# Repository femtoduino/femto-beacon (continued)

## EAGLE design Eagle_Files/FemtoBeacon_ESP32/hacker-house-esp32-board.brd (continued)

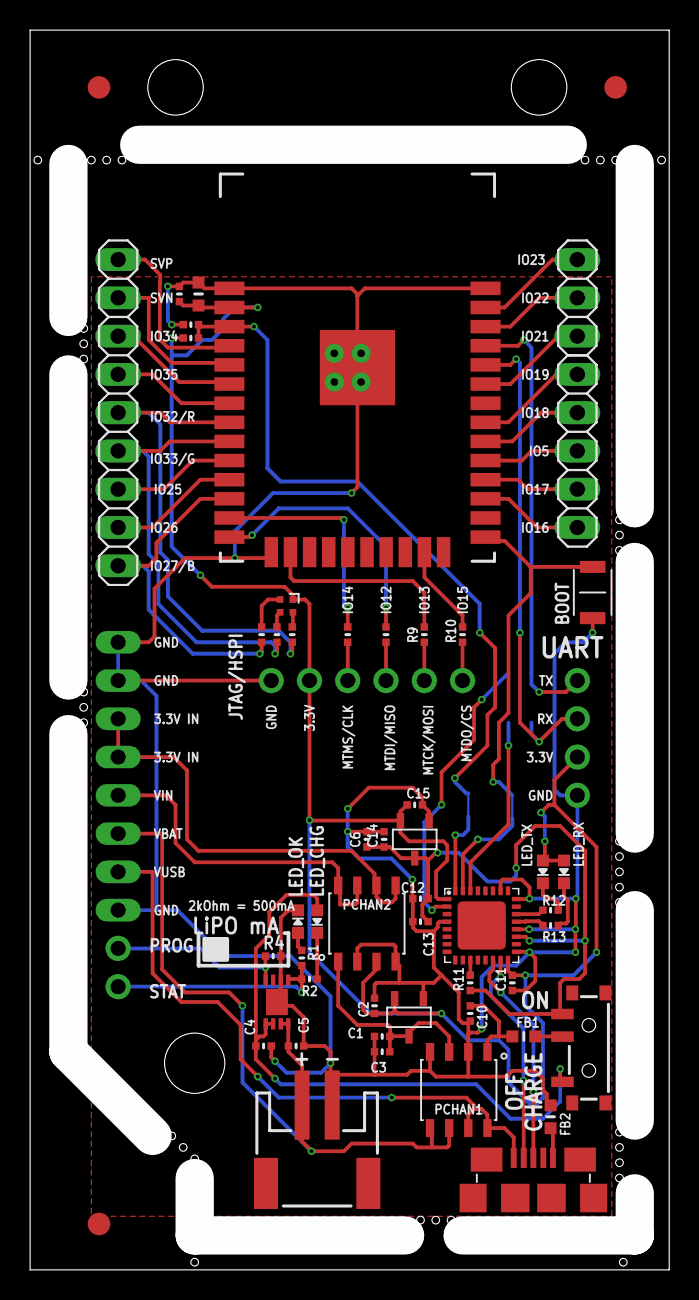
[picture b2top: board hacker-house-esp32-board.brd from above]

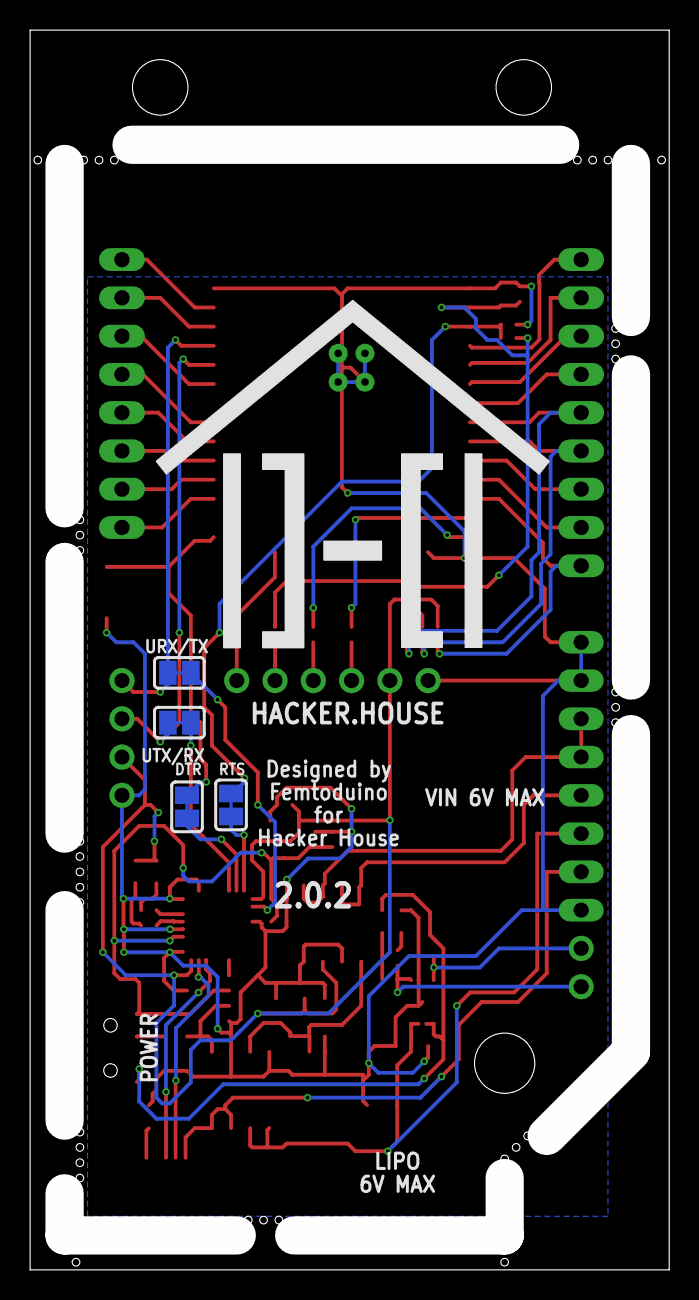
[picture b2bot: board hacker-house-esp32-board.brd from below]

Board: 2 copper layers, 42.4 x 82.3 mm, 62 parts (4 on the bottom side), 57 nets.

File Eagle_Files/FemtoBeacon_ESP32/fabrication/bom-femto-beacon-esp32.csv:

"Qty";"Value";"Device";"Package";"Parts";"Description";"MF";"MPN";"OC_FARNELL";"OC_NEWARK";
"2";"";"FERRITE_0603MP";"_0603MP";"FB1, FB2";"Ferrite Bead";"";"";"";"";
"2";"";"HEADER-1X1ROUND";"1X01_ROUND";"PROG, STAT";"PIN HEADER";"";"";"";"";
"1";"";"HEADER-1X4ROUND";"1X04_ROUND";"UART";"PIN HEADER";"";"";"";"";
"1";"";"HEADER-1X6SMT";"1X06_SMT";"JTAG";"PIN HEADER";"";"";"";"";
"1";"";"HEADER-1X7ROUND";"1X07_ROUND";"SPI";"PIN HEADER";"";"";"";"";
"1";"";"HEADER-1X8";"1X08_OVAL";"POWER";"PIN HEADER";"";"";"";"";
"1";"";"JST_2PIN";"JSTPH2";"CN_BATT_CHARGE";"JST 2-Pin Right-Angle Connector";"";"S2B-PH-SM4-TB(LF)(SN)";"";"";
"1";"";"PINHD-1X3";"1X03";"JP4";"PIN HEADER";"";"";"";"";
"1";"";"PINHD-1X6";"1X06";"JP3";"PIN HEADER";"";"";"";"";
"1";"";"PINHD-1X9";"1X09";"JP1";"PIN HEADER";"";"";"";"";
"3";"";"RESISTOR_0402MP";"_0402MP";"R14, R15, R16";"Resistors";"";"";"";"";
"3";"";"SOLDERJUMPERCLOSED";"SOLDERJUMPER_CLOSEDWIRE";"SJ1, SJ2, SJ3";"SMD Solder JUMPER";"";"";"";"";
"3";"";"SWITCH_SPDT";"SPDT_SMT_SSSS811101";"SWCHARGE, SWPOWER, SW_BATTMODE";"Switch - SPDT";"";"SSSS811101";"";"";
"6";"";"TESTPOINTROUND0.5MM";"TESTPOINT_ROUND_0.5MM";"TP1, TP2, TP3, TP4, TP5, TP6";"Test Point";"";"";"";"";
"1";"";"USB_TYPEA";"USB_A-SMT";"CN1";"USB - Type A Connectors";"";"36-931-ND";"";"";
"5";"0.1uF";"CAP_CERAMIC_0402MP";"_0402MP";"C6, C8, C9, C11, C13";"Ceramic Capacitors";"";"";"";"";
"1";"0.47uF";"CAP_CERAMIC_0402MP";"_0402MP";"C3";"Ceramic Capacitors";"";"";"";"";
"4";"100";"RESISTOR_0402MP";"_0402MP";"R7, R8, R9, R10";"Resistors";"";"";"";"";
"1";"100k";"RESISTOR_0402MP";"_0402MP";"R5";"Resistors";"";"";"";"";
"3";"10K";"RESISTOR_0402MP";"_0402MP";"R4, R6, R11";"Resistors";"";"";"";"";
"1";"10nF";"CAP_CERAMIC_0402MP";"_0402MP";"C10";"Ceramic Capacitors";"";"";"";"";
"1";"10uF";"CAP_CERAMIC_0603MP";"_0603MP";"C7";"Ceramic Capacitors";"";"";"";"";
"2";"2.2uF";"CAP_CERAMIC_0402MP";"_0402MP";"C1, C2";"Ceramic Capacitors";"";"";"";"";
"1";"2.5k";"RESISTOR_0402MP";"_0402MP";"R3";"Resistors";"";"";"";"";
"2";"221";"RESISTOR_0402MP";"_0402MP";"R1, R2";"Resistors";"";"";"";"";
"2";"270";"RESISTOR_0402MP";"_0402MP";"R12, R13";"Resistors";"";"";"";"";
"1";"3.3V";"MCP1700T-3302E/TT";"MCP1700T-3302E/TT";"LDO1";"Microchip LDO "MCP1700" in a 3-Pin SOT-23 package.";"";"MCP1700T-3302E/TT";"";"";
"3";"4.7uF";"CAP_CERAMIC_0402MP";"_0402MP";"C4, C5, C12";"Ceramic Capacitors";"";"";"";"";
"1";"ESP32-WROOM-32";"ESP32-WROOM-32";"ESP32-WROOM-32-MODULE";"MOD1";"ESP32 WiFi/Bluetooth module";"";"ESP32-WROOM-32";"";"";
"3";"FIDUCIAL";"FIDUCIAL";"FIDUCIAL_1MM";"FID1, FID2, FID3";"For use by pick and place machines to calibrate the vision/machine, 1mm";"";"";"";"";
"1";"FT232RQ";"FT232RQ";"QFN32";"IC1";"Source: http://www.ftdichip.com/Documents/DataSheets/DS_FT232R_v104.pdf";"";"FT232RQ";"1146033";"91K9919";
"3";"GREEN";"LED0603_NOOUTLINE";"CHIPLED_0603_NOOUTLINE";"LED_OK, LED_RX, LED_TX";"LED";"";"";"";"";
"1";"LRTB_R48G";"LRTB_R48G";"LRTB_R48G";"RGB1";"OSRAM RGB LED";"";"LRTB R48G";"";"";
"1";"MCP73831-2ACI/MC";"MCP73831-2ACI/MC";"2X3_DFN";"LIPO1";"";"";"MCP73831-2ACI/MC";"";"";
"1";"RED";"LED0603_NOOUTLINE";"CHIPLED_0603_NOOUTLINE";"LED_CHG";"LED";"";"";"";"";
"2";"SI4948BEY-T1-E3";"SI4948BEY-T1-E3";"SO-8";"PCHAN1, PCHAN2";"Vishay dual P-Channel Mosfet SI4948BEY-T1-E3";"";"SI4948BEY-T1-E3";"";"";
"1";"TACTILE_SWITCH_NO_GND_NO_BOSS";"TACTILE_SWITCH_NO_GND_NO_BOSS";"SIDE_ACT_NO_GND_NO_BOSS";"BOOT";"Omron tactile switch";"";"B3U-3000P";"";"";

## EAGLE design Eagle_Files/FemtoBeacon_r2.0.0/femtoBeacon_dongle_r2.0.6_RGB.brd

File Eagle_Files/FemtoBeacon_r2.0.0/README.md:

eagle-pcb-helpers
=================

A collection of JS utilities to help with Eagle PCB grunt work.

## Panelizer helper
A utility to help you panelize stuff outside the board size limits.

### Requires

 - Node http-server `npm install -g http-server`

### Usage
Use a terminal, navigate to this folder, and run `http-server ./`, then open up [https://localhost:8080/panelizer_helper.html](https://localhost:8080/panelizer_helper.html) in your favorite browser.

### About
Due to the artificially (and arbitrarily) imposed board size limitations of EAGLE PCB licensing, it becomes impossible to panelize large amounts of small boards.
This tool allows one to copy a column of board outlines, components, and text, and create the corresponding XML with updated part names (such as "IC1...IC5" to "IC6...IC10", etc), while applying a shift value to the X coordinates.

You still need to manually open the .brd file, and locate the last column of `<element>` nodes, but you can simply copy and paste that XML into this helper, set an X offset value, and process the text to generate the next column.

EAGLE PCB doesn't have any problem copying vias and traces outside the artificial boundry limits, so you really only need this tool for dimensions and components.

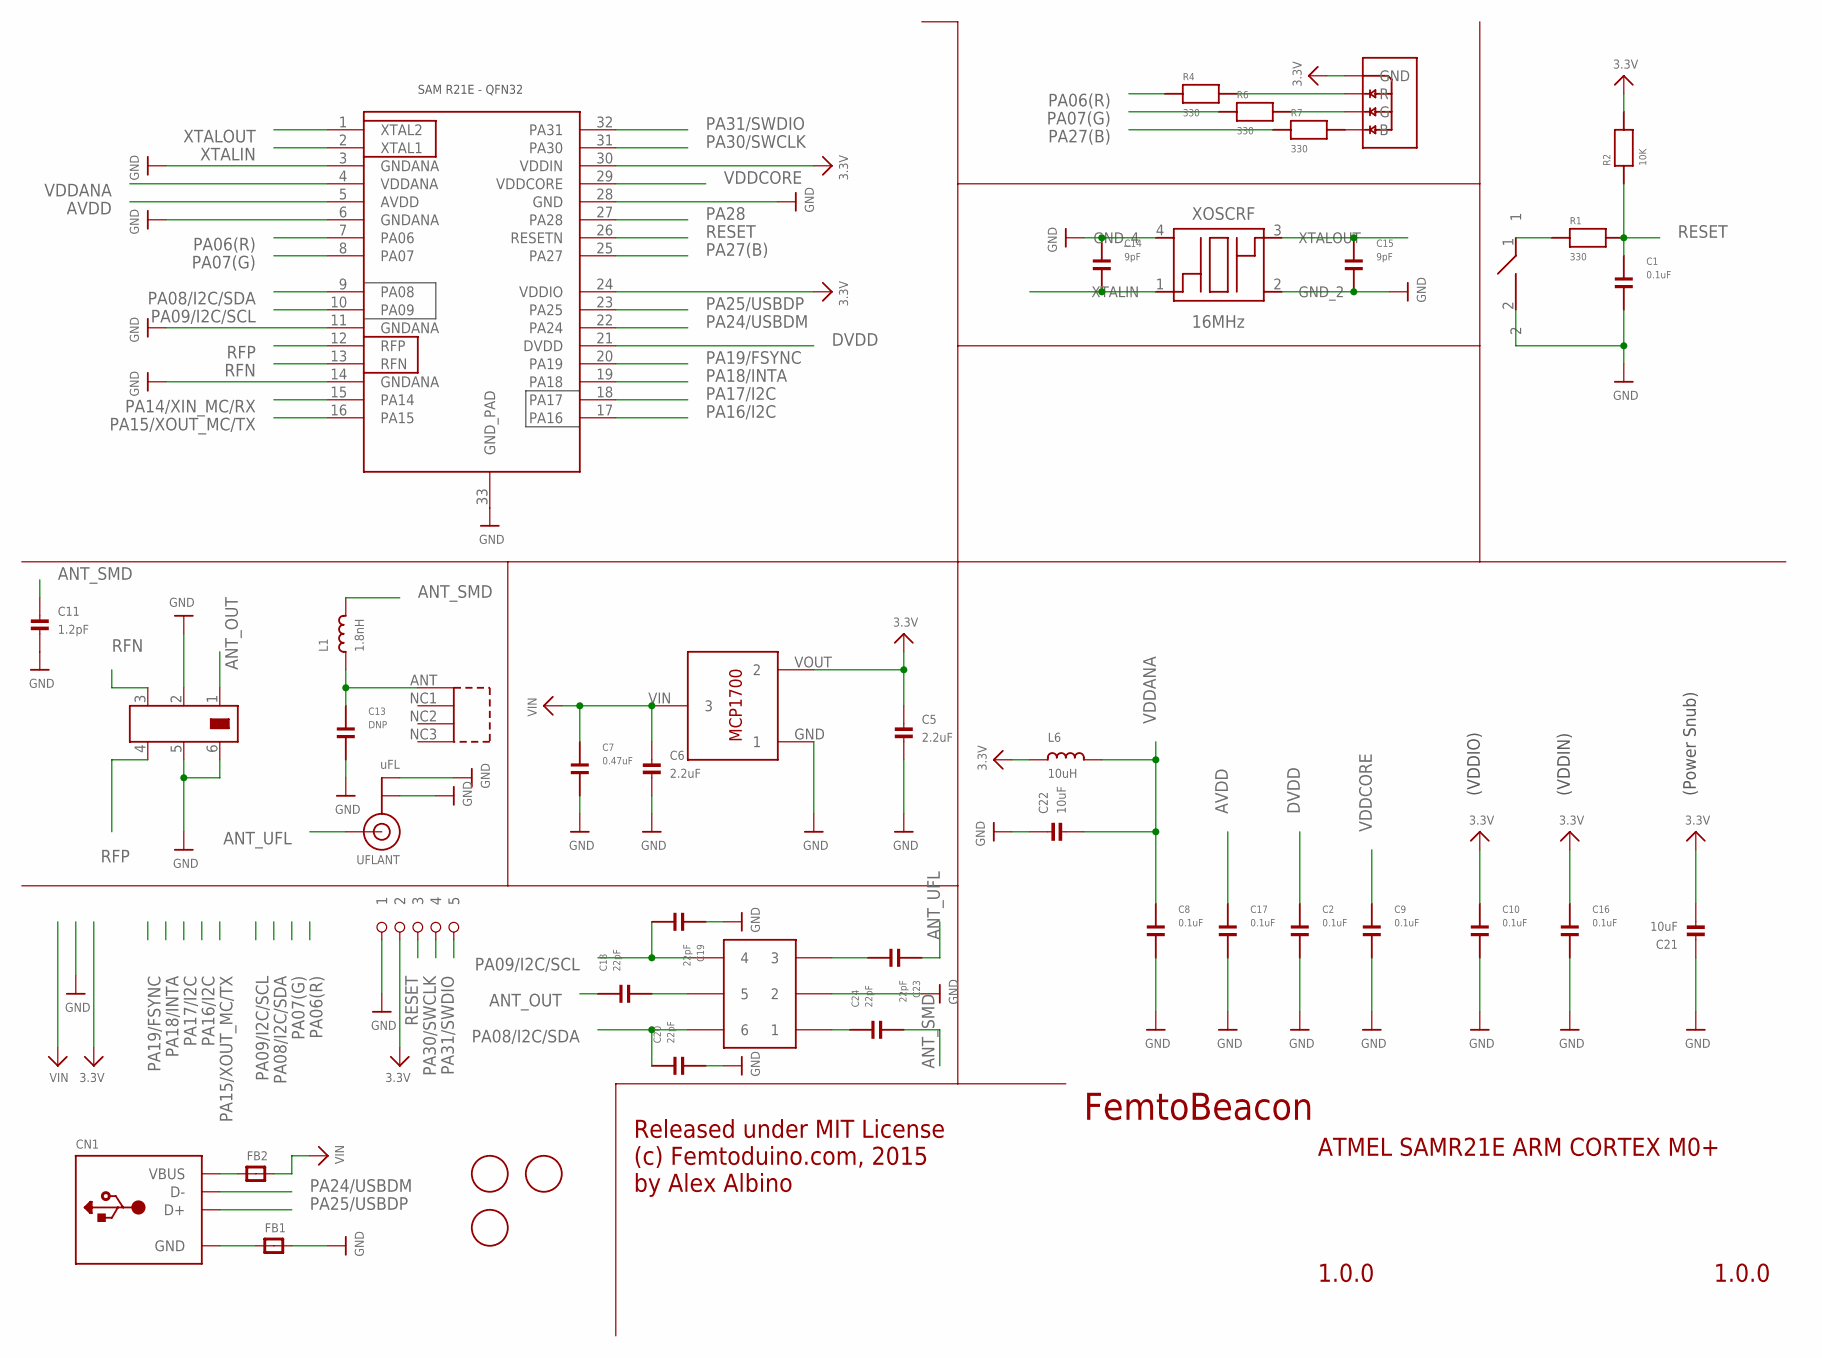
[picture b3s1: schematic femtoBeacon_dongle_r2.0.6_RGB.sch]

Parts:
ASWITCH: AS222-92LF
BTN: DNP; SPST_SMD
C1, C2, C8, C9, C10, C16, C17: 0.1uF; PART
C5, C6: 2.2uF; _0402MP
C7: 0.47uF; PART
C11: 1.2pF; _0402MP
C13: DNP; PART
C14, C15: 9pF; PART
C18, C19, C20, C23, C24: 22pF; PART
C21, C22: 10uF; _0402MP
CN1: USB_TYPEA; USB_A-SMT
FB1, FB2: FERRITE_0603MP; _0603MP
FID1, FID2, FID3: FIDUCIAL; FIDUCIAL_1MM
L1: 1.8nH; _0603MP
L6: 10uH; _0603MP
LDO_VREG: MCP1700T-3302E/TT
R1, R4, R6, R7: 330; PART
R2: 10K; PART
RGBLED: LRTB_R48G
U$1: 1X5_ROUND
U$6: 0479480001
U$12: JOHANSON_2450BM15A0015E; 0805_BALUN
U$76: ATSAMR21E18A-MUT; QFN32
UFLANT: uFL; U.FL
XOSCRF: 16MHz; TSX-3225

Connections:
3.3V: C5.1, C10.1, C16.1, C21.2, L6.1, LDO_VREG.VOUT (2), R2.2, RGBLED.1 (GND), U$1.P$2 (2), U$76.24 (VDDIO), U$76.30 (VDDIN)
ANT_LINE: C13.1, L1.1, U$6.ANT (1)
ANT_OUT: C18.1, U$12.1
ANT_SMD: C11.1, C24.2, L1.2
ANT_UFL: C23.1, UFLANT.3 (SIGNAL)
AVDD: C17.1, U$76.5 (AVDD)
DVDD: C2.1, U$76.21 (DVDD)
GND: ASWITCH.PIN2 (2), BTN.2, C1.2, C2.2, C5.2, C6.2, C7.2, C8.2, C9.2, C10.2, C11.2, C13.2, C14.1, C15.2, C16.2, C17.2, C19.1, C20.2, C21.1, C22.1, FB1.2, LDO_VREG.GND (1), U$1.P$1 (1), U$12.2, U$12.5, U$12.6, U$76.3 (GNDANA), U$76.6 (GNDANA), U$76.11 (GNDANA), U$76.14 (GNDANA), U$76.28 (GND), U$76.33 (GND_PAD), UFLANT.1 (GND), UFLANT.2 (GND), XOSCRF.2 (GND_2), XOSCRF.4 (GND_4)
unnamed: R6.2, RGBLED.3 (G)
unnamed: CN1.VBUS, FB2.1
unnamed: CN1.GND, FB1.1
unnamed: R7.2, RGBLED.4 (B)
unnamed: R4.2, RGBLED.2 (R)
unnamed: BTN.1, R1.1
PA06(R): R4.1, U$76.7 (PA06)
PA07(G): R6.1, U$76.8 (PA07)
PA08/I2C/SDA: ASWITCH.PIN6 (6), C20.1, U$76.9 (PA08)
PA09/I2C/SCL: ASWITCH.PIN4 (4), C19.2, U$76.10 (PA09)
PA14/XIN_MC/RX: U$76.15 (PA14)
PA15/XOUT_MC/TX: U$76.16 (PA15)
PA16/I2C: U$76.17 (PA16)
PA17/I2C: U$76.18 (PA17)
PA18/INTA: U$76.19 (PA18)
PA19/FSYNC: U$76.20 (PA19)
PA24/USBDM: CN1.D-, U$76.22 (PA24)
PA25/USBDP: CN1.D+, U$76.23 (PA25)
PA27(B): R7.1, U$76.25 (PA27)
PA28: U$76.27 (PA28)
PA30/SWCLK: U$1.P$4 (4), U$76.31 (PA30)
PA31/SWDIO: U$1.P$5 (5), U$76.32 (PA31)
RESET: C1.1, R1.2, R2.1, U$1.P$3 (3), U$76.26 (RESETN)
RFN: U$12.3, U$76.13 (RFN)
RFP: U$12.4, U$76.12 (RFP)
RFSWITCH_PIN1: ASWITCH.PIN1 (1), C24.1
RFSWITCH_PIN3: ASWITCH.PIN3 (3), C23.2
RFSWITCH_PIN5: ASWITCH.PIN5 (5), C18.2
VDDANA: C8.1, C22.2, L6.2, U$76.4 (VDDANA)
VDDCORE: C9.1, U$76.29 (VDDCORE)
VIN: C6.1, C7.1, FB2.2, LDO_VREG.VIN (3)
XTALIN: C14.2, U$76.2 (XTAL1), XOSCRF.1 (XTALIN)
XTALOUT: C15.1, U$76.1 (XTAL2), XOSCRF.3 (XTALOUT)

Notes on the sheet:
FemtoBeacon
1.0.0
ATMEL SAMR21E ARM CORTEX M0+
Released under MIT License (c) Femtoduino.com, 2015 by Alex Albino
(Power Snub)
(VDDIO)
(VDDIN)

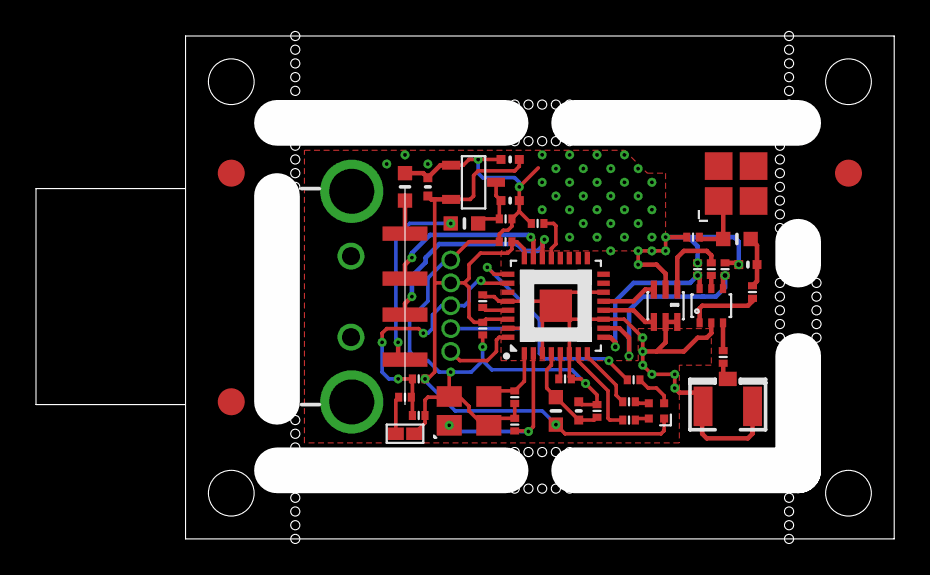
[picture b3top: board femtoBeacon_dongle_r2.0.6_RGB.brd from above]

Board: 2 copper layers, 47.7 x 27.9 mm, 44 parts (0 on the bottom side), 34 nets.

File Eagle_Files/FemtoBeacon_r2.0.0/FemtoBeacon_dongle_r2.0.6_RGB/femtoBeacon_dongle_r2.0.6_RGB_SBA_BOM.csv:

##########################################################################
       Name: Placement Bill of Materials Generator

    Version: 4 (2-sided, top)
         By: Small Batch Assembly
        URL: www.smallbatchassembly.com
 SourceFile: femtoBeacon_dongle_r2.0.6_RGB.brd
   DateTime: 1/3/18 4:22 AM
      Units: inches
##########################################################################
REF,PACKAGE,VALUE,X,Y,ROTATION,
ASWITCH   , AS222-92LF            , AS222-92LF     , 1.1500, 0.5100, 0.0
BTN   , SPST_SMD            , DNP     , 0.4800, 0.2300, 0.0
C1   , PART            , 0.1uF     , 0.5100, 0.2700, 0.0
C2   , PART            , 0.1uF     , 0.7700, 0.6900, 180.0
C5   , _0402MP            , 2.2uF     , 0.7100, 0.8300, 180.0
C6   , _0402MP            , 2.2uF     , 0.7100, 0.7400, 0.0
C7   , PART            , 0.47uF     , 0.7000, 0.7000, 0.0
C8   , PART            , 0.1uF     , 0.9000, 0.2800, 90.0
C9   , PART            , 0.1uF     , 0.6500, 0.5200, 90.0
C10   , PART            , 0.1uF     , 0.7000, 0.6500, 180.0
C11   , _0402MP            , 1.2pF     , 1.2300, 0.6000, 180.0
C13   , PART            , DNP     , 1.1100, 0.6600, 180.0
C14   , PART            , 9pF     , 0.7200, 0.2500, 270.0
C15   , PART            , 9pF     , 0.7200, 0.3100, 270.0
C16   , PART            , 0.1uF     , 0.6500, 0.4600, 270.0
C17   , PART            , 0.1uF     , 0.8300, 0.3500, 0.0
C18   , PART            , 22pF     , 1.1500, 0.5900, 270.0
C19   , PART            , 22pF     , 1.1800, 0.5900, 270.0
C20   , PART            , 22pF     , 1.1200, 0.5900, 90.0
C21   , _0402MP            , 10uF     , 0.5300, 0.7700, 270.0
C22   , _0402MP            , 10uF     , 0.8600, 0.2800, 270.0
C23   , PART            , 22pF     , 1.1760, 0.3980, 90.0
C24   , PART            , 22pF     , 1.2400, 0.5400, 90.0
CN1   , USB_A-SMT            ,      , 0.4800, 0.5300, 90.0
FB1   , _0603MP            ,      , 0.4800, 0.7700, 90.0
FB2   , _0603MP            ,      , 0.6100, 0.6900, 0.0
FID1   , FIDUCIAL_1MM            , FIDUCIAL     , 0.1000, 0.3000, 0.0
FID2   , FIDUCIAL_1MM            , FIDUCIAL     , 0.1000, 0.8000, 0.0
FID3   , FIDUCIAL_1MM            , FIDUCIAL     , 1.4500, 0.8000, 0.0
L1   , _0603MP            , 1.8nH     , 1.2060, 0.6560, 0.0
L6   , _0603MP            , 10uH     , 0.8100, 0.2800, 90.0
LDO_VREG   , MCP1700T-3302E/TT            , MCP1700T-3302E/TT     , 0.6300, 0.7800, 270.0
R1   , PART            , 330     , 0.4800, 0.3100, 0.0
R2   , PART            , 10K     , 0.5100, 0.3500, 0.0
R4   , PART            , 330     , 0.9700, 0.2600, 0.0
R6   , PART            , 330     , 0.9700, 0.3000, 0.0
R7   , PART            , 330     , 0.9800, 0.3480, 0.0
RGBLED   , LRTB_R48G            , LRTB_R48G     , 1.0300, 0.2800, 270.0
U$6   , 0479480001            , 0479480001     , 1.2040, 0.7770, 90.0
U$12   , 0805_BALUN            , JOHANSON_2450BM15A0015E     , 1.0500, 0.5100, 270.0
U$76   , QFN32            , ATSAMR21E18A-MUT     , 0.8100, 0.5100, 90.0
UFLANT   , U.FL            , uFL     , 1.1860, 0.2900, 90.0
XOSCRF   , TSX-3225            , 16MHz     , 0.6200, 0.2800, 0.0

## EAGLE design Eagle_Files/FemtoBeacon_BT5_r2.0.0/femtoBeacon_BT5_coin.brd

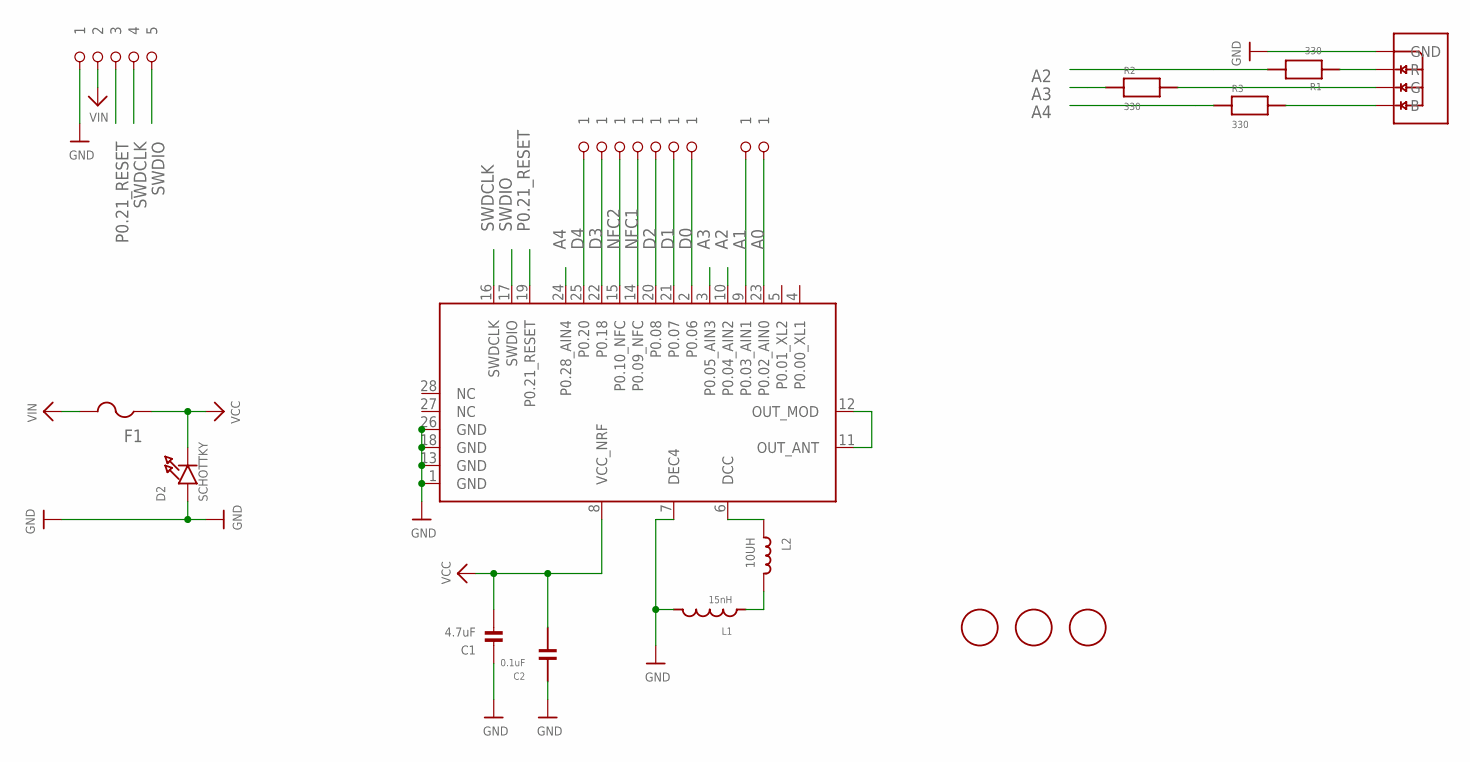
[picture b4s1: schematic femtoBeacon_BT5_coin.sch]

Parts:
C1: 4.7uF; _0402MP
C2: 0.1uF; PART
D2: SCHOTTKY; CHIPLED_0603_NOOUTLINE
F1: PTCFUSE-1206; R1206
FID1, FID2, FID3: FIDUCIAL; FIDUCIAL_1MM
IC: TY_BLE_EYSHSNZWZ; MODULE
L1: 15nH; PART
L2: 10UH; _0402MP
LED1: LRTB_R48G
R1, R2, R3: 330; PART
U$6: 1X5_ROUND
U$16, U$17, U$18, U$19, U$20, U$21, U$22, U$23, U$24: 1X1_ROUND_MM

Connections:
A0: IC.23 (P0.02_AIN0), U$16.P$1
A1: IC.9 (P0.03_AIN1), U$17.P$1
A2: IC.10 (P0.04_AIN2), R1.2
A3: IC.3 (P0.05_AIN3), R2.1
A4: IC.24 (P0.28_AIN4), R3.1
D0: IC.2 (P0.06), U$18.P$1
D1: IC.21 (P0.07), U$19.P$1
D2: IC.20 (P0.08), U$20.P$1
D3: IC.22 (P0.18), U$23.P$1
D4: IC.25 (P0.20), U$24.P$1
GND: C1.1, C2.1, D2.A, IC.1 (GND), IC.7 (DEC4), IC.13 (GND), IC.18 (GND), IC.26 (GND), L1.2, LED1.1 (GND), U$6.P$1 (1)
INTERNAL_ANT: IC.11 (OUT_ANT), IC.12 (OUT_MOD)
unnamed: IC.6 (DCC), L2.1
unnamed: LED1.2 (R), R1.1
unnamed: L1.1, L2.2
unnamed: LED1.3 (G), R2.2
unnamed: LED1.4 (B), R3.2
NFC1: IC.14 (P0.09_NFC), U$21.P$1
NFC2: IC.15 (P0.10_NFC), U$22.P$1
P0.21_RESET: IC.19 (P0.21_RESET), U$6.P$3 (3)
SWDCLK: IC.16 (SWDCLK), U$6.P$4 (4)
SWDIO: IC.17 (SWDIO), U$6.P$5 (5)
VCC: C1.2, C2.2, D2.C, F1.1, IC.8 (VCC_NRF)
VIN: F1.2, U$6.P$2 (2)

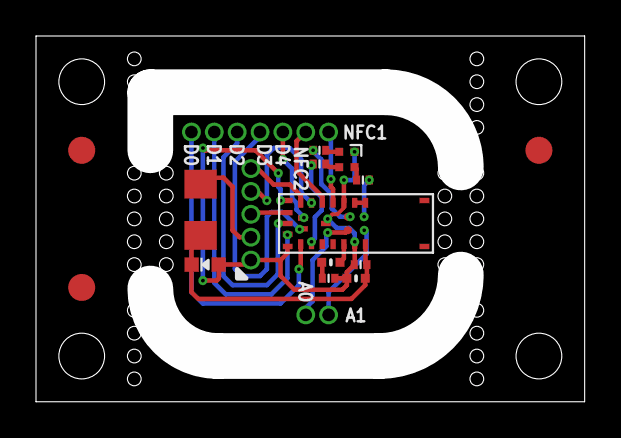
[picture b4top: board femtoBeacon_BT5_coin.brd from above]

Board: 2 copper layers, 30.5 x 20.3 mm, 24 parts (0 on the bottom side), 24 nets.

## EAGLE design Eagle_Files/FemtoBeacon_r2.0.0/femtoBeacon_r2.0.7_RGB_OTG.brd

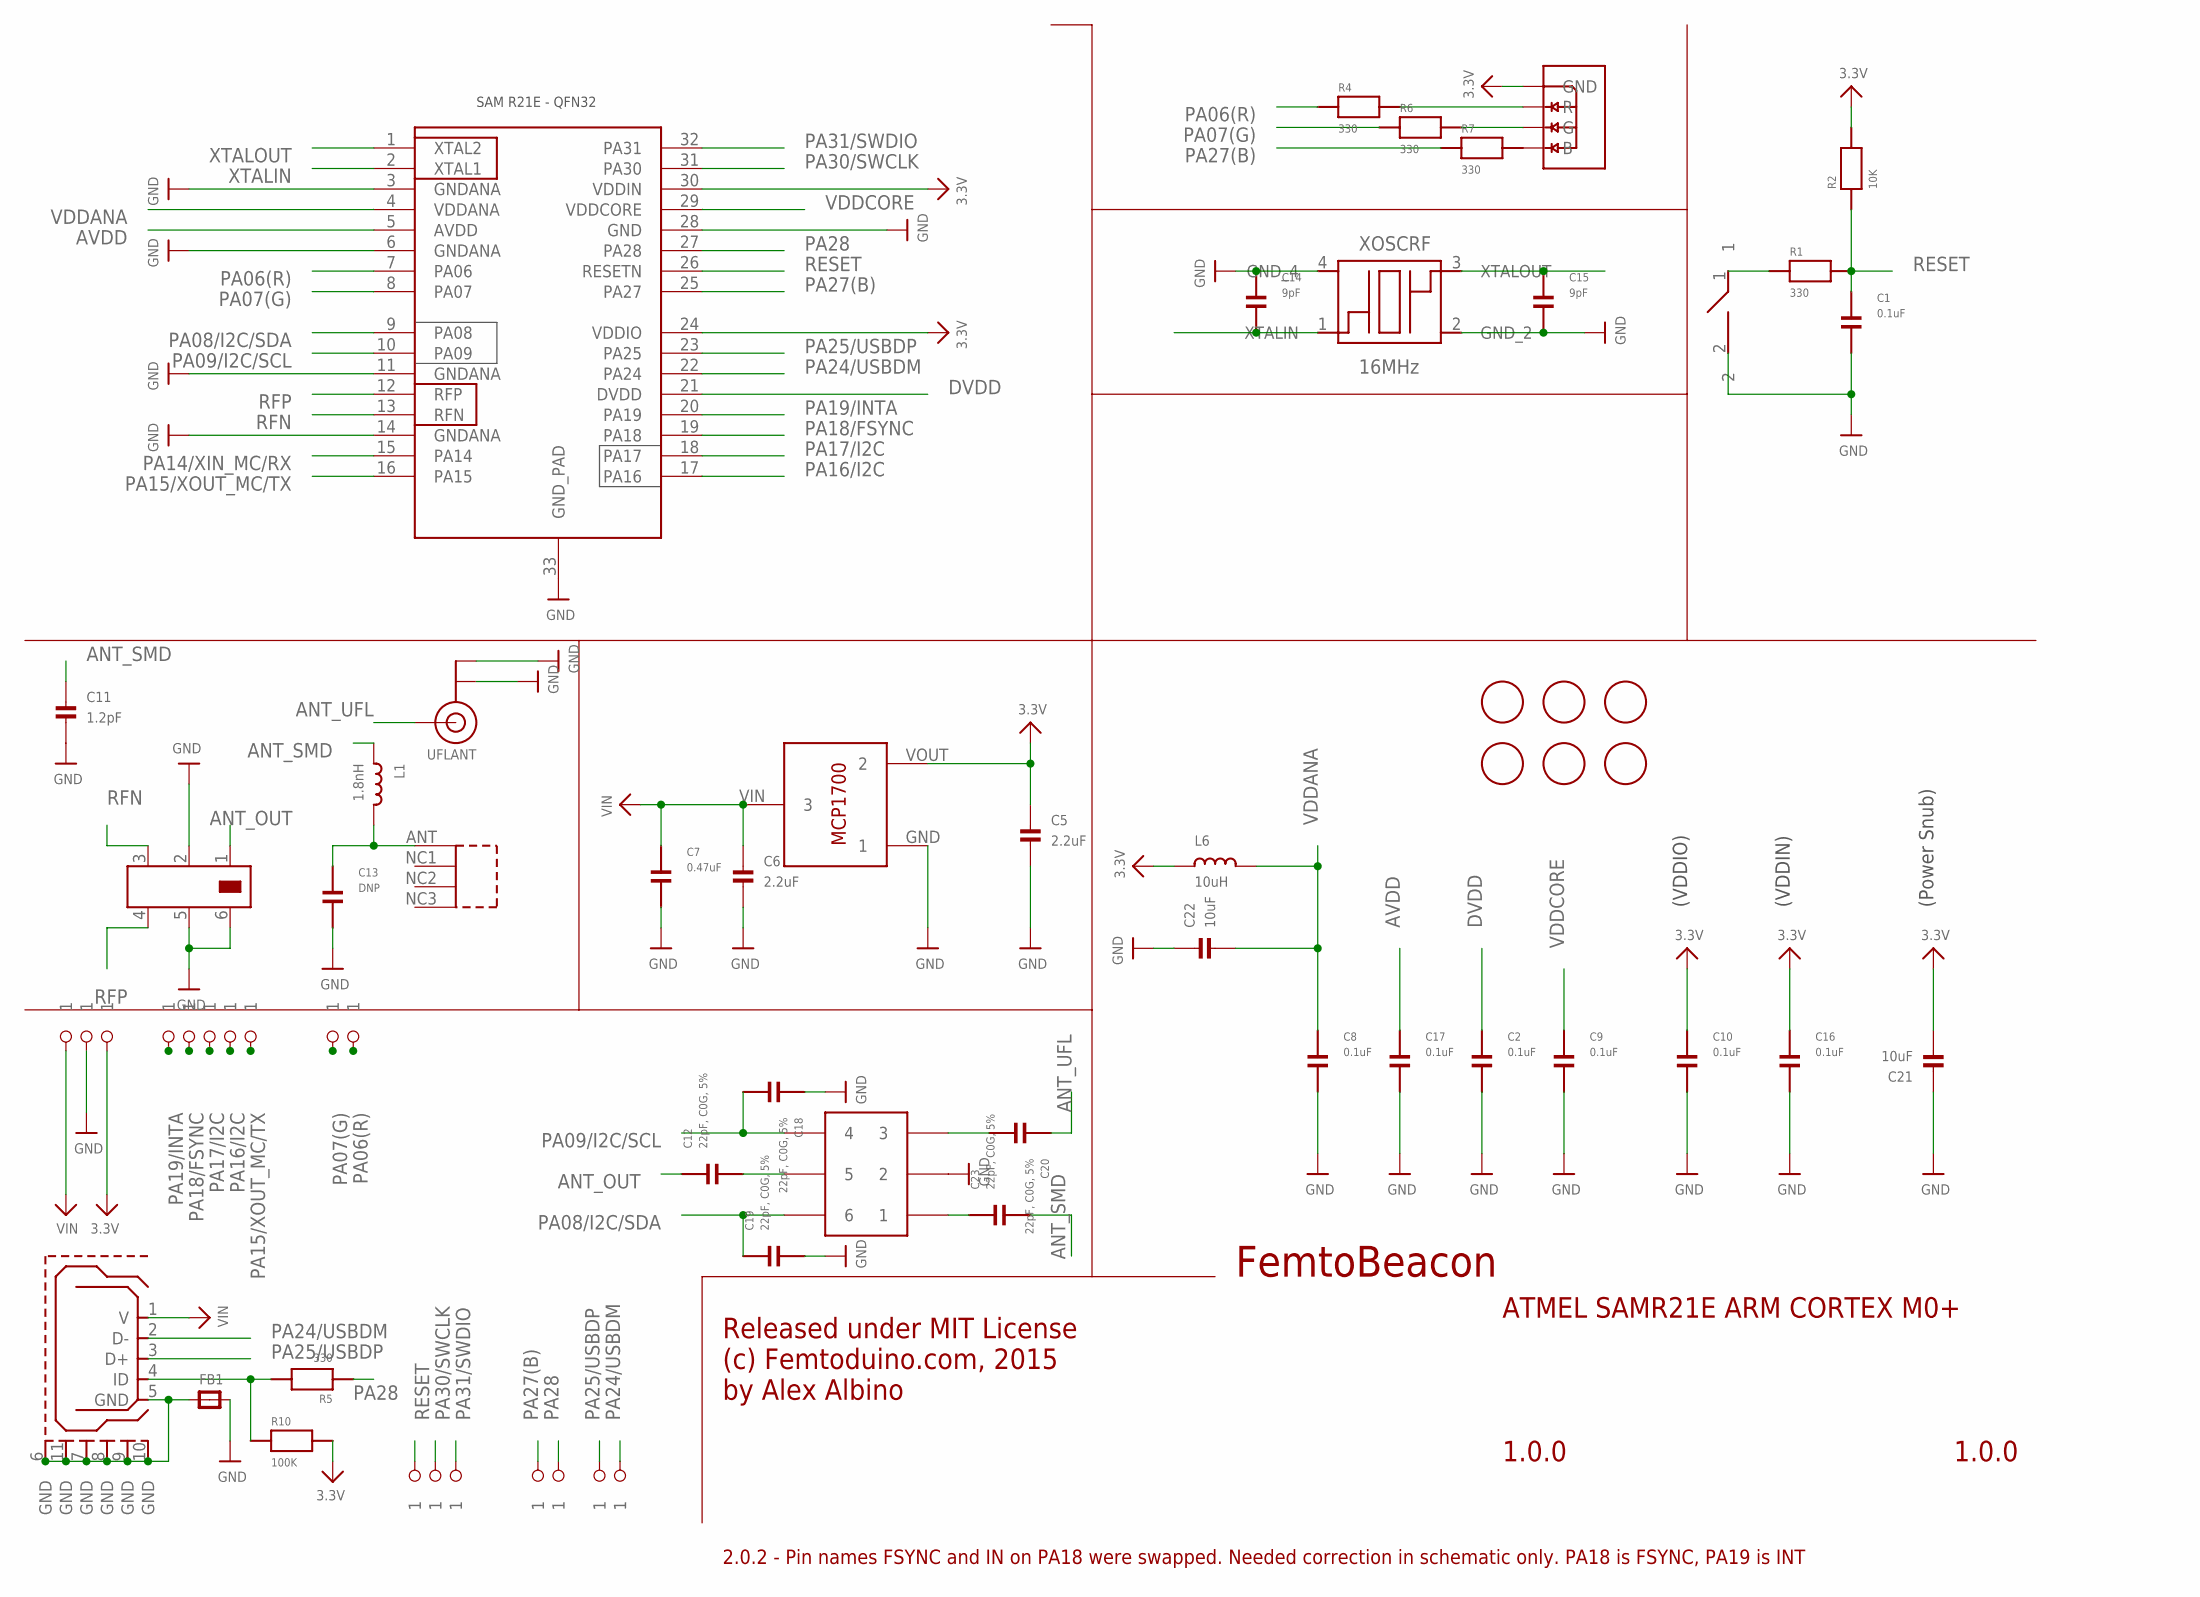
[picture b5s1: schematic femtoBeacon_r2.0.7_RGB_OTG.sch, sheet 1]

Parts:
ANT_SMD: 0479480001
ASWITCH: AS222-92LF
BALUN: JOHANSON_2450BM15A0015E; 0805_BALUN
BTN: DNP; SPST_SMD
C1, C8, C9, C10, C16, C17: 0.1uF; PART; DIGIKEY_PART 490-3194-1-ND
C2: 0.1uF; PART
C5, C6: 2.2uF; _0402MP
C7: 0.47uF; PART
C11: 1.2pF; _0402MP
C12, C18, C19, C20, C23: 22pF, C0G, 5%; PART; DIGIKEY_PART 490-3194-1-ND
C13: DNP; PART; DIGIKEY_PART 490-3194-1-ND
C14, C15: 9pF; PART; DIGIKEY_PART 490-3194-1-ND
C21, C22: 10uF; _0402MP
FB1: FERRITE_0603MP; _0603MP
FID1, FID2, FID3, FID4, FID5, FID6: FIDUCIAL; FIDUCIAL_1MM
IC: ATSAMR21E18A-MUT; QFN32
L1: 1.8nH; _0603MP
L6: 10uH; _0603MP
LDO_VREG: MCP1700T-3302E/TT
R1, R4, R5, R6, R7: 330; PART
R2: 10K; PART
R10: 100K; PART
RGBLED: LRTB_R48G
U$1, U$2, U$5, U$7, U$9, U$10, U$35, U$36, U$37, U$38, U$39, U$43, U$45, U$46, U$47, U$48, U$54: 1X1_ROUND
UFLANT: ANTENNA_U.FL; U.FL
USB: USB_MICROB; USB_MICROB_PACKAGE
XOSCRF: 16MHz; TSX-3225

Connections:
3.3V: C5.1, C10.1, C16.1, C21.2, IC.24 (VDDIO), IC.30 (VDDIN), L6.1, LDO_VREG.VOUT (2), R2.2, R10.2, RGBLED.1 (GND), U$5.P$1; also elsewhere on the board
ANT_LINE: ANT_SMD.ANT (1), C13.1, L1.2
ANT_OUT: BALUN.1, C12.1
ANT_SMD: C11.1, C23.2, L1.1
ANT_UFL: C20.1, UFLANT.3 (SIGNAL)
AVDD: C17.1, IC.5 (AVDD)
DVDD: C2.1, IC.21 (DVDD)
GND: ASWITCH.PIN2 (2), BALUN.2, BALUN.5, BALUN.6, BTN.2, C1.2, C2.2, C5.2, C6.2, C7.2, C8.2, C9.2, C10.2, C11.2, C13.2, C14.1, C15.2, C16.2, C17.2, C18.1, C19.2, C21.1, C22.1, FB1.2, IC.3 (GNDANA), IC.6 (GNDANA), IC.11 (GNDANA), IC.14 (GNDANA), IC.28 (GND), IC.33 (GND_PAD), LDO_VREG.GND (1), U$2.P$1, UFLANT.1 (GND), UFLANT.2 (GND), XOSCRF.2 (GND_2), XOSCRF.4 (GND_4); also elsewhere on the board
unnamed: R5.2, R10.1, USB.4 (ID)
unnamed: FB1.1, USB.5 (GND), USB.6 (GND), USB.7 (GND), USB.8 (GND), USB.9 (GND), USB.10 (GND), USB.11 (GND)
unnamed: R6.2, RGBLED.3 (G)
unnamed: R7.2, RGBLED.4 (B)
unnamed: R4.2, RGBLED.2 (R)
unnamed: BTN.1, R1.1
PA06(R): IC.7 (PA06), R4.1, U$54.P$1
PA07(G): IC.8 (PA07), R6.1, U$43.P$1
PA08/I2C/SDA: ASWITCH.PIN6 (6), C19.1, IC.9 (PA08)
PA09/I2C/SCL: ASWITCH.PIN4 (4), C18.2, IC.10 (PA09)
PA14/XIN_MC/RX: IC.15 (PA14)
PA15/XOUT_MC/TX: IC.16 (PA15), U$39.P$1
PA16/I2C: IC.17 (PA16), U$38.P$1; also elsewhere on the board
PA17/I2C: IC.18 (PA17), U$37.P$1; also elsewhere on the board
PA18/FSYNC: IC.19 (PA18), U$36.P$1; also elsewhere on the board
PA19/INTA: IC.20 (PA19), U$35.P$1; also elsewhere on the board
PA24/USBDM: IC.22 (PA24), U$9.P$1, USB.2 (D-)
PA25/USBDP: IC.23 (PA25), U$10.P$1, USB.3 (D+)
PA27(B): IC.25 (PA27), R7.1, U$7.P$1
PA28: IC.27 (PA28), R5.1, U$48.P$1
PA30/SWCLK: IC.31 (PA30), U$46.P$1
PA31/SWDIO: IC.32 (PA31), U$47.P$1
RESET: C1.1, IC.26 (RESETN), R1.2, R2.1, U$45.P$1
RFN: BALUN.3, IC.13 (RFN)
RFP: BALUN.4, IC.12 (RFP)
RFSWITCH_PIN1: ASWITCH.PIN1 (1), C23.1
RFSWITCH_PIN3: ASWITCH.PIN3 (3), C20.2
RFSWITCH_PIN5: ASWITCH.PIN5 (5), C12.2
VDDANA: C8.1, C22.2, IC.4 (VDDANA), L6.2
VDDCORE: C9.1, IC.29 (VDDCORE)
VIN: C6.1, C7.1, LDO_VREG.VIN (3), U$1.P$1, USB.1 (V)
XTALIN: C14.2, IC.2 (XTAL1), XOSCRF.1 (XTALIN)
XTALOUT: C15.1, IC.1 (XTAL2), XOSCRF.3 (XTALOUT)

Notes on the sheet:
FemtoBeacon
1.0.0
ATMEL SAMR21E ARM CORTEX M0+
Released under MIT License (c) Femtoduino.com, 2015 by Alex Albino
(Power Snub)
(VDDIO)
(VDDIN)
2.0.2 - Pin names FSYNC and IN on PA18 were swapped. Needed correction in schematic only. PA18 is FSYNC, PA19 is INT

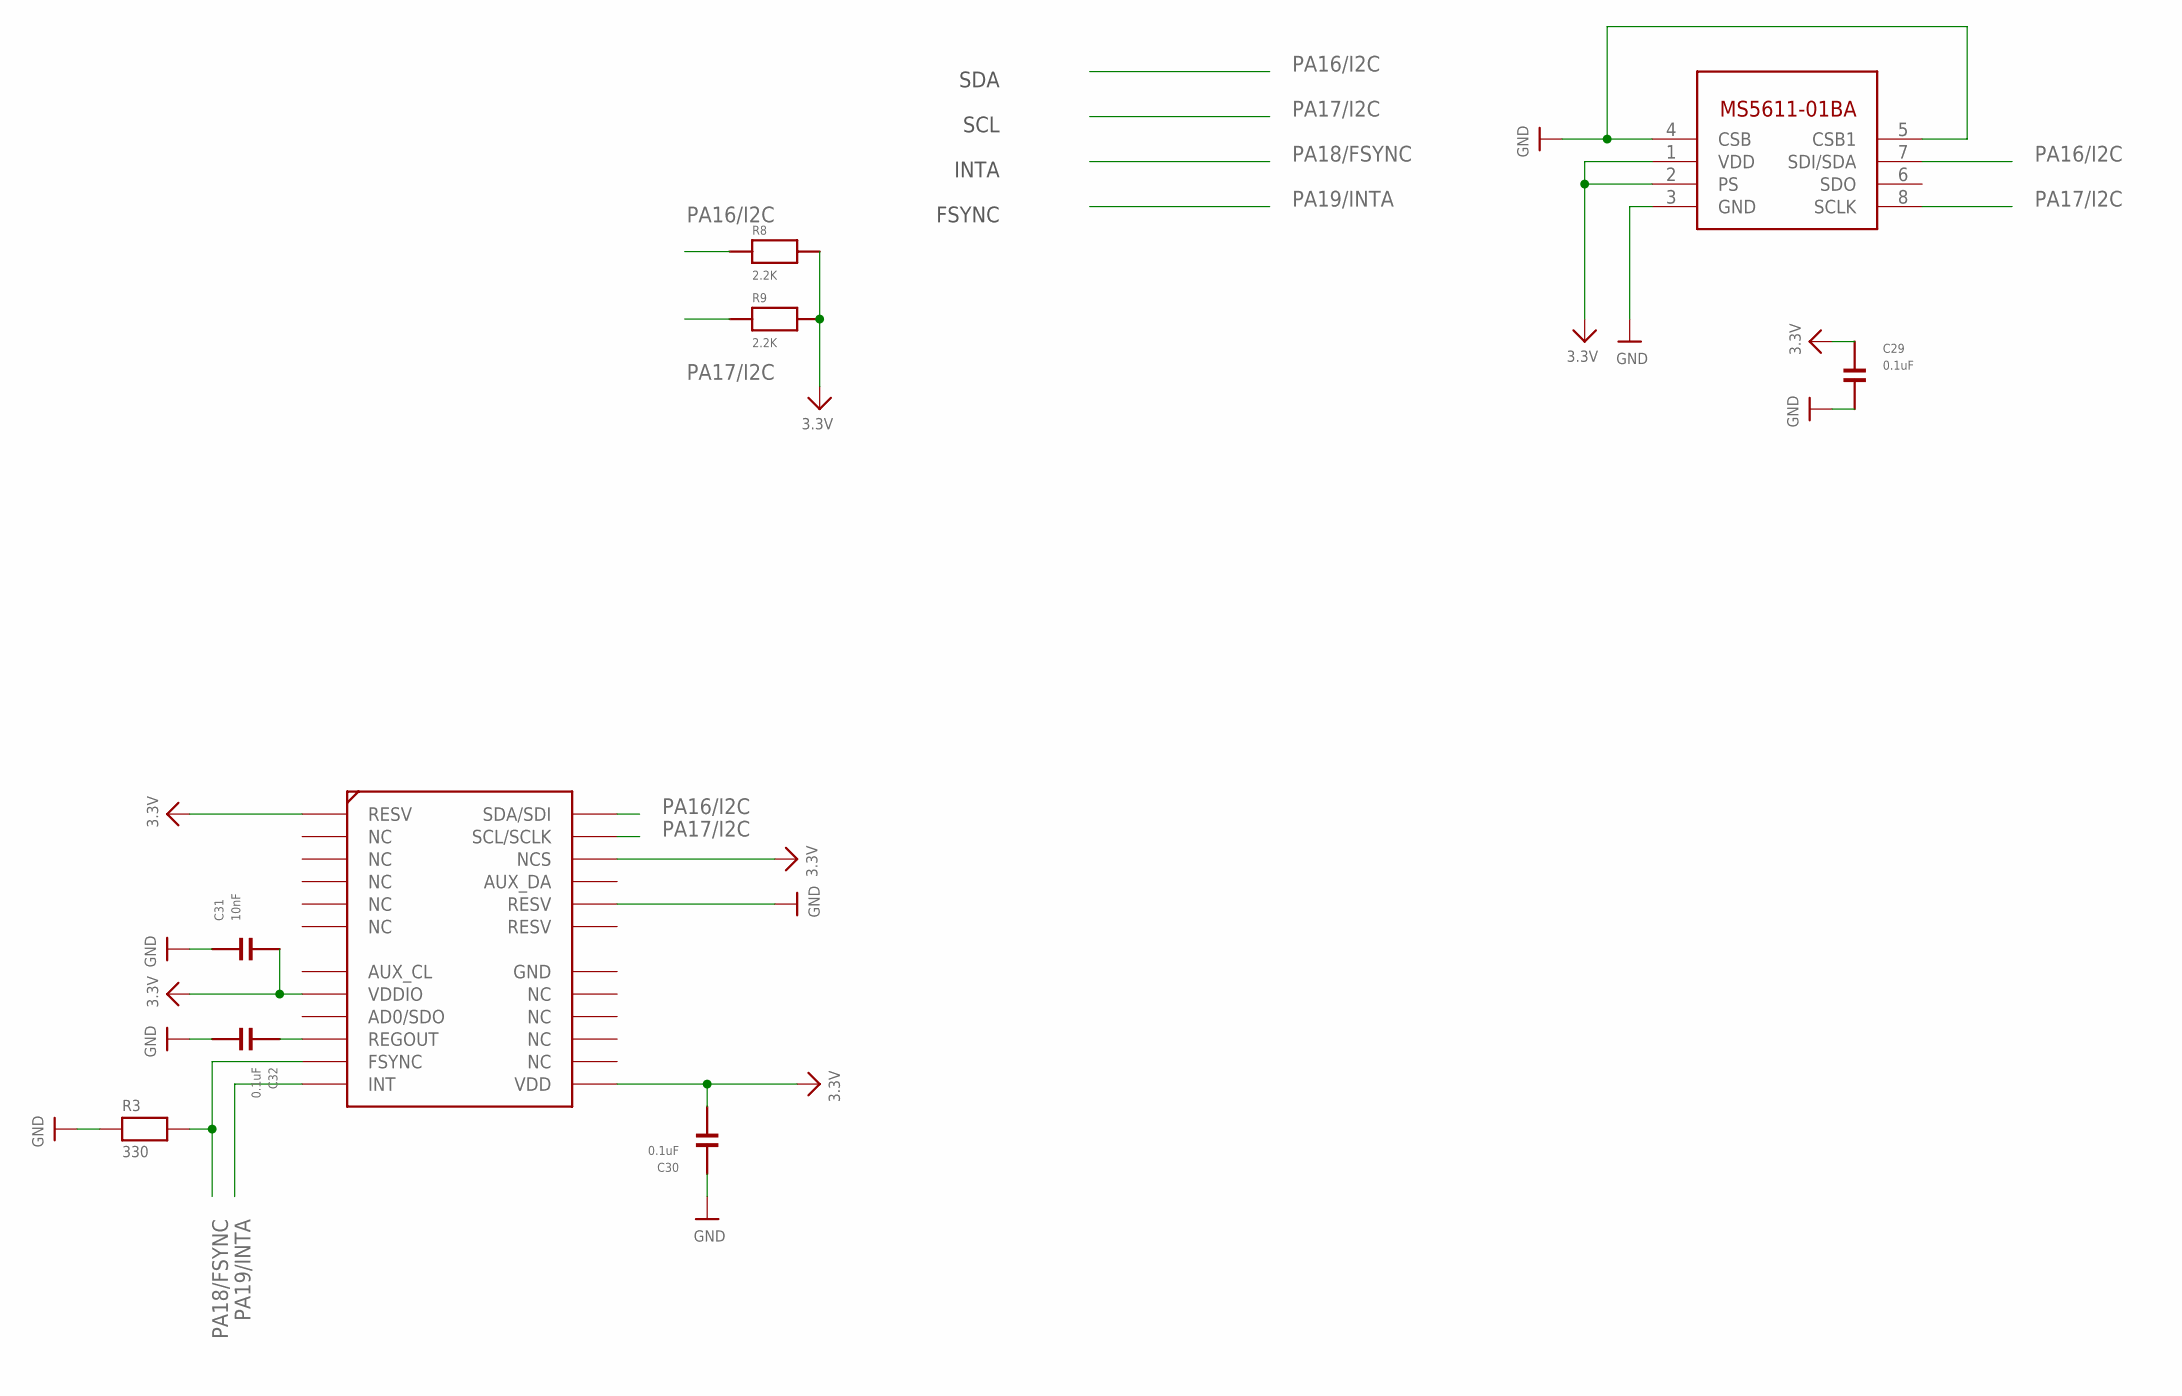
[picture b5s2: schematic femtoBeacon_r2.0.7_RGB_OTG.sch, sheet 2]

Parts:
BARO: MS5611-01BA03
C29, C30, C32: 0.1uF; PART; DIGIKEY_PART 490-3194-1-ND
C31: 10nF; PART; DIGIKEY_PART 490-3194-1-ND
IMU: MPU-9250; QFN_3X3MM
R3: 330; _0402
R8, R9: 2.2K; PART

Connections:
3.3V: BARO.1 (VDD), BARO.2 (PS), C29.1, C30.2, C31.2, IMU.P$1 (RESV), IMU.P$8 (VDDIO), IMU.P$13 (VDD), IMU.P$22 (NCS), R8.2, R9.2; also elsewhere on the board
GND: BARO.3 (GND), BARO.4 (CSB), BARO.5 (CSB1), C29.2, C30.1, C31.1, C32.2, IMU.P$20 (RESV), R3.1; also elsewhere on the board
unnamed: C32.1, IMU.P$10 (REGOUT)
PA16/I2C: BARO.7 (SDI/SDA), IMU.P$24 (SDA/SDI), R8.1; also elsewhere on the board
PA17/I2C: BARO.8 (SCLK), IMU.P$23 (SCL/SCLK), R9.1; also elsewhere on the board
PA18/FSYNC: IMU.P$11 (FSYNC), R3.2; also elsewhere on the board
PA19/INTA: IMU.P$12 (INT); also elsewhere on the board

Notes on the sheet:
SDA
SCL
INTA
FSYNC
